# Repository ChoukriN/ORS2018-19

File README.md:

# ORS2018-19
ORS SARE Project Repository

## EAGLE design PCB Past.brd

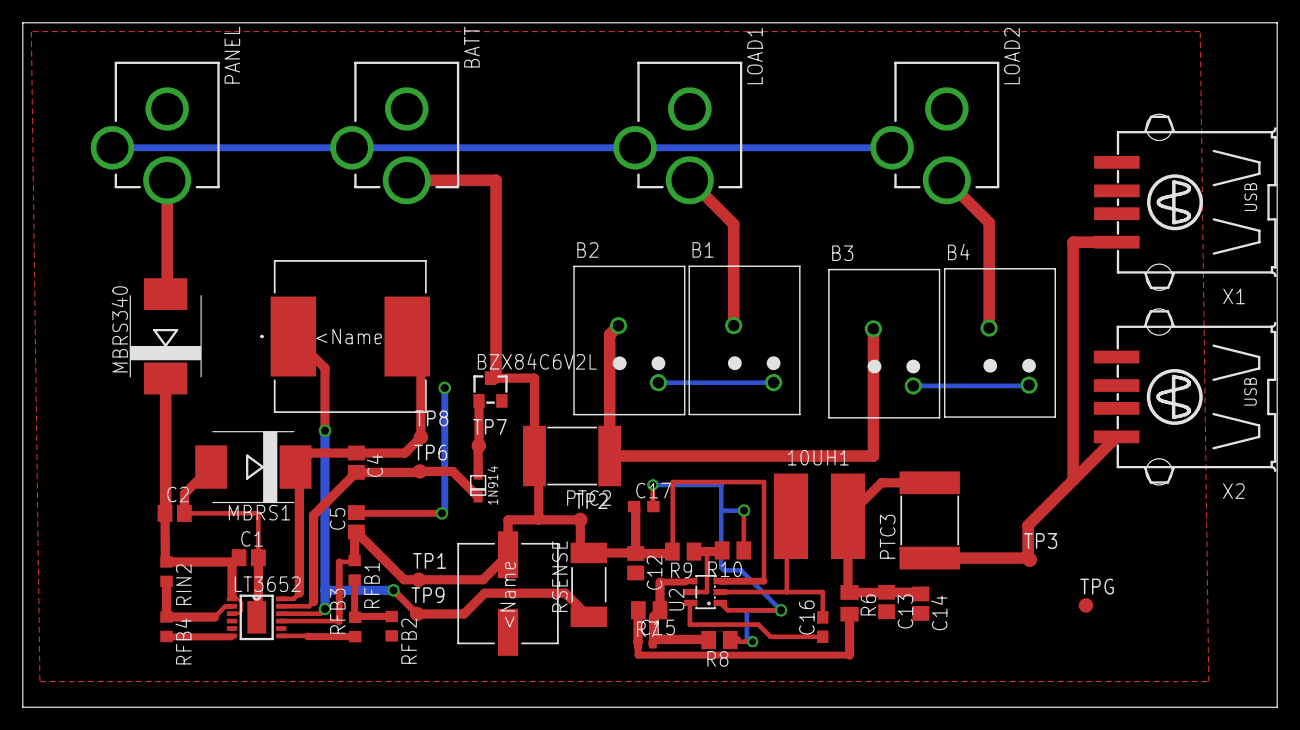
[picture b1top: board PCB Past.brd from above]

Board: 2 copper layers, 110.0 x 60.0 mm, 50 parts (0 on the bottom side), 24 nets.

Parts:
1N914: Rectifier; SOD-323F
10UH1: SDE0805A
B1, B2, B3, B4: TERMINALBLOCK
BATT: J4; DCJACK_2MM_PTH
BZX84C6V2L: Zener; TO236
C1, C2, C5, C12: 10uF; C0805
C3: 100uF; CAP_EEFK_E
C4: 1uF; C0805
C13, C14: 22uF; C0805
C15: 75pF; C0402
C16, C17: .1uF; C0603
L1: 22uH; IND_BOURNS_SRR1205
LOAD1: J3; DCJACK_2MM_PTH
LOAD2: J4; DCJACK_2MM_PTH
LT3652: LT3645MSE; MSOP12
MBRS1, MBRS340: Schottky; SMC
PANEL: J1; DCJACK_2MM_PTH
PTC2, PTC3: 2920L300/15; 2920L
R6: 49.9; M0805
R7: 100k; M0805
R8: 13.3k; M0805
R9: 1M; M0805
R10: 187k; M0805
RFB1: 309K; R0603
RFB2, RFB4: 100K; R0603
RFB3: 174K; R0603
RIN2: 499K; R0603
RSENSE: .05; R2512
TP1, TP2, TP3, TP6, TP7, TP8, TP9: TPB1,27; B1,27
TPG: TPB1,27; B1,27
U2: TPS54302; SOT23-6
X1, X2: USB-A003

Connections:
GND: BATT.GND, C1.2, C2.2, C3.1, C5.2, C12.2, C13.2, C14.2, C17.2, LOAD1.GND, LOAD2.GND, LT3652.6, LT3652.EXP, MBRS1.A, PANEL.GND, R8.1, R10.1, RFB2.2, RFB4.2, TPG.TP, U2.1, X1.4, X2.4
unnamed: C1.1, C2.1, LT3652.1, LT3652.3, MBRS340.C, RIN2.1
unnamed: LT3652.7, RFB3.1
unnamed: RFB1.2, RFB2.1, RFB3.2
unnamed: LT3652.2, RFB4.1, RIN2.2
unnamed: MBRS340.A, PANEL.PWR
unnamed: 1N914.C, C4.2, LT3652.11, TP6.TP
unnamed: 1N914.A, BZX84C6V2L.A, TP7.TP
unnamed: BATT.PWR, BZX84C6V2L.C, C3.2, C5.1, C12.1, C17.1, LT3652.9, PTC2.2, R9.2, RFB1.1, RSENSE.2, TP1.TP, TP2.TP, U2.3
unnamed: B2.BACK, B3.BACK, PTC2.1
unnamed: L1.1, LT3652.10, RSENSE.1, TP9.TP
unnamed: C4.1, L1.2, LT3652.12, MBRS1.C, TP8.TP
unnamed: 10UH1.R, C13.1, C14.1, PTC3.2, R6.1
unnamed: B3.FRONT, B4.FRONT
unnamed: BATT.GNDBREAK, LOAD1.GNDBREAK, LOAD2.GNDBREAK, PANEL.GNDBREAK
unnamed: B1.FRONT, B2.FRONT
unnamed: C15.1, R6.2, R7.2
unnamed: R9.1, R10.2, U2.5
unnamed: 10UH1.L, C16.2, U2.2
unnamed: C16.1, U2.6
unnamed: C15.2, R7.1, R8.2, U2.4
unnamed: B1.BACK, LOAD1.PWR
unnamed: B4.BACK, LOAD2.PWR
VOUT: PTC3.1, TP3.TP, X1.1, X2.1

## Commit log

2018-10-30 add files
